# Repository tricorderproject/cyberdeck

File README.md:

# Open Source Science Tricorder Cyberdeck

Explore alien planets with... the open source science tricorder cyberdeck!

# What is this

This is the Github Repository for the **Open Source Science Tricorder Cyberdeck**, an open-source hardware tricorder-like device similar in function to some of the science tricorder devices from the science fiction series Star Trek.  These devices essentially pack a large number of scientific sensors into small hand-held devices, with the (science fiction) intent being that they would be broadly useful for exploring alien worlds, and making new scientific discoveries.

# Table of Contents

- [What is this](#what-is-this)
- [Pictures](#pictures)
- [Frequently Asked Questions](#frequently-asked-questions)
- [Sensor/Hardware List](#sensorhardware-list)
  - [UConsole](#uconsole)
  - [Main Sensors](#main-sensors)
- [Custom PCBs](#custom-pcbs)
  - [PCB: Hamamatsu Microspectrometer Breakout](#pcb-hamamatsu-microspectrometer-breakout)
  - [PCB: ESP32 Breakout](#pcb-esp32-breakout)
  - [PCB: USB Hub Breakout](#pcb-usb-hub-breakout)
- [3D Printed Components](#3d-printed-components)
  - [3D Print: Main Body](#3d-print-main-body)
  - [3D Print: Back Plate](#3d-print-back-plate)
  - [3D Print: Magnetometer Top and Bottom](#3d-print-magnetometer-top-and-bottom)
  - [3D Print: Power Switch](#3d-print-power-switch)
- [Physical Assembly Video](#physical-assembly-video)
- [Firmware (ESP32)](#firmware-esp32)
- [User Interface (Python/UConsole)](#user-interface-pythonuconsole)
- [Design Philosophy and Iterations](#design-philosophy-and-iterations)
  - [Where it was coming from: The Arducorder Mini](#where-it-was-coming-from-the-arducorder-mini)
  - [Iteration 8: Attaching something to an iPhone](#iteration-8-attaching-something-to-an-iphone)
  - [Iteration 9: Teensycorder: Trying to make something that looked like a BlackBerry](#iteration-9-teensycorder-trying-to-make-something-that-looked-like-a-blackberry)
  - [Iteration 10: T-Deck-Corder](#iteration-10-t-deck-corder)
  - [Iteration 11: Initial Cyberdeck explorations with the BTree](#iteration-11-initial-cyberdeck-explorations-with-the-btree)
  - [Iteration 12: A smaller Cyberdeck with the Clockwork Pi PicoCalc](#iteration-12-a-smaller-cyberdeck-with-the-clockwork-pi-picocalc)
  - [Iteration 13: The Open Source Science Tricoder Cyberdeck](#iteration-13-the-open-source-science-tricoder-cyberdeck)
- [Errata](#errata)
  - [Things that are real errors](#things-that-are-real-errors)
  - [Things that I just don't like, or that aren't implemented yet](#things-that-i-just-dont-like-or-that-arent-implemented-yet)
- [AI Usage](#ai-usage)
- [License](#license)
- [Warranty](#warranty)
- [Contact](#contact)

# Pictures

| Main Screen | Spectrometer Screen | Magnetic imager in use (1) | Magnetic imager in use (2) |
| :---: | :---: | :---: | :---: |
|  |  |  |  |
| **Main body with components** | **Main body and back cover** | **Assembled (from back)** | |
|  |  |  | |

# Frequently Asked Questions

**Q1: What is a tricorder?**

A tricorder is a fictional device from the TV series Star Trek, that characters (like Spock) would take with them when they traveled to alien planets.  The tricorder is essentially like a box full of sensors, that would tell them all sorts of things about the environments they would travel to -- like detecting lifeforms, helping them make discoveries, or solve whatever challenges they faced.  There are nominally two kinds of tricorders in the shows -- medical tricorders (that they use for medical diagnosis), and the science tricorders, which they use for scientific/exploratory tasks. 

**Q2. What can it sense?**

This currently has the following sensing capabilities:
- **Thermal Imaging:** a 80x62 Waveshare imager, paired with a regular visible USB camera
- **Visible Spectroscopy:** a Hamamatsu C12666MA microspectrometer, with 256 spectral channels between 340nm and 780nm (in practice, the spectral resolution is about 15nm)
- **Magnetic Field Imager:** An 8x8 (64 pixel) magnetic field camera, provided by the Sparkfun Magnetic Imaging Tile. In practice this can go up to about 20KHz (i.e. 20,000 frames per second). This is also paired with a regular magnetometer (MLX90393) for magnetic field strength and direction.
- **Radiation Spectroscopy:** Where previous open source science tricorders have included radiation sensors, this version includes the Pomelo radiation spectroscopy detector, which uses a scintillation crystal and can differentiate energy levels.
- **Environmental Sensors:** CO2 level, VOC level, Air particulate matter (e.g. PM1/2.5/4/10), ambient temperature, pressure, and humidity.

**Q3: What is a cyberdeck?**

A cyberdeck is the name for essentially small handheld consoles (that include small screens and keyboards), that frequently run full operating systems, and that are often designed to be hackable/modified.  This build is based on the [UConsole by Clockwork Pi](https://www.clockworkpi.com/home-uconsole), which uses a Raspberry Pi compute module -- so it runs linux, and has several cores, about 4GB of RAM, and lots of eMMC storage. 

**Q4: Are there videos showing it functioning?**

Yes, [here is a video on Youtube](https://youtube.com/shorts/MCvRtOt6pII) showing its main functionality. 

**Q5: Is there a video of it being assembled/the inside?**

Yes!  [Here is a video of the inside being put together](https://youtube.com/shorts/LsJ3JqqFUqU), component by component.

**Q6: What does open source mean in the context of open hardware?**

Open hardware is like open source software, except that it is the designs for the device that are openly shared/distributed.  The software/firmware for the device is also included. 

**Q7: Can I build this?**

The honest answer is -- maybe.  This is a prototype, not a product, and there are lots of rough edges.  Historically, most of the utility from the past releases of the open source science tricorders seems to be educational, inspirational (i.e. a real tricorder-like device!), or derivatives (e.g. folks using part of the designs for their own work).  The devices are quite complex to build, and quite expensive.  

**Q8: Why did you build this?**

I grew up watching Star Trek, and my first career choice was always space explorer -- it just turned out that I was born a little early for that to be a common occupation.  But we're not going to get there just sitting around -- we make the future ourselves, so let's build the technology to become future explorers, and make new discoveries together.

**Q9: Who was this made by?**

The Open Source Science Tricorder Project is an open-source educational outreach by Dr. Peter Jansen, a professor at the University of Arizona.  You can learn more about me [here](https://cognitiveai.org/).

**Q10: How many past open source science tricoders have their been?**

I have made about a dozen designs, but only four (including this cyberdeck) have been official 'releases' with significant documentation, the others are generally iterations or prototypes (and some of the failed prototypes for this cyberdeck design are shown in the section below, since it's always exciting to see the development process!). I used to post a design blog on the process, but I am a little busy these days, and don't have a lot of free time, so it now takes me longer to build these things than I am willing to admit. 

The past major releases are the [Mark 1](https://tricorderproject.org/tricorder-mark1.html) and [Mark2 2](https://tricorderproject.org/tricorder-mark2.html) in 2012, the [Arducorder Mini](https://hackaday.io/project/1395-open-source-science-tricorder) in 2014, and then this Cyberdeck in 2026.  In the interim, I also worked on other educational open source hardware projects, like the open source computed tomography (CT) scanners. 

**Q11: How much did this Cyberdeck cost to build?**

The UConsole itself, CM4 compute module, and associated HackerGadgets extension boards, are likely around $300-$400, while the components and build here are likely around $1000.  The visible microspectrometer and the pomelo radiation spectrometer are by far the most expensive components.

# Sensor/Hardware List

The following is the core hardware used in this device, including links to datasheets/etc.

## UConsole

| Component | Description | Link |
| --- | --- | --- |
| UConsole | Clockwork Pi UConsole | [ClockworkPi](https://www.clockworkpi.com/home-uconsole) |
| UConsole Extension | Internal USB Hub, CM5 adapter, battery board | [Hacker Gadgets](https://hackergadgets.com/products/uconsole-upgrade-kit) |

## Main Sensors

| Component | Description | Link |
| --- | --- | --- |
| Thermal Camera | Waveshare Long-wave IR Camera (80x62, USB C) | [Waveshare](https://www.waveshare.com/thermal-camera.htm?sku=25288) |
| USB Camera | Waveshare IMX378 12MP | [Waveshare](https://www.waveshare.com/imx378-12mp-usb-camera-a.htm) |
| Microspectrometer | Hamamatsu C12666MA | [Hamamatsu](https://www.hamamatsu.com/us/en/product/optical-sensors/spectrometers/mini-spectrometer/C12666MA.html) |
| Radiation Sensor | Pomelo Spectroscopic Radiation Detector | [Crowd Supply](https://www.crowdsupply.com/pomelo-instrumentation/pomelo) |
| Air Particle Sensor | Sensirion Particulate Matter Sensor SPS30 | [Sensirion](https://sensirion.com/products/catalog/SPS30) |
| Magnetic Imaging Tile | SparkFun Magnetic Imaging Tile - 8x8 | [SparkFun](https://www.sparkfun.com/sparkfun-magnetic-imaging-tile-8x8.html) |
| Magnetometer | MLX90393 Breakout | [SparkFun](https://www.sparkfun.com/sparkfun-triple-axis-magnetometer-breakout-mlx90393-qwiic.html) |
| CO2 Sensor | SCD40 CO2/Temp/Humidity Breakout | [SparkFun](https://www.sparkfun.com/sparkfun-co2-humidity-and-temperature-sensor-scd40-qwiic.html) |
| Environmental Sensor | BME680 Temp/Pressure/Humidity/VOC | [SparkFun](https://www.sparkfun.com/sparkfun-environmental-sensor-breakout-bme680-qwiic.html) |
| QWIIC Hub | SparkFun Qwiic MultiPort | [SparkFun](https://www.sparkfun.com/sparkfun-qwiic-multiport.html) |

In addition to the hardware above, a handful of custom PCBs are used (described below).

# Custom PCBs

While effort was made to try and have everything in the device be off-the-shelf for this build, a handful of boards were used to make things a little more compact. 

## PCB: Hamamatsu Microspectrometer Breakout

This is a small breakout for the Hamamatsu CD12666MA microspectrometer, that primarily provides a low-profile connector, an op-amp buffer, and handful of filtering passives to help keep the power clean. 

| Board (front) | Board (back) | PCB (top) | PCB (bottom) |
| :---: | :---: | :---: | :---: |
|  |  |  |  |
| **Reflow (toaster oven)** | | | |
|  | | | |

**Design files (EAGLE 9.6.2):** [Schematic (PDF)](hardware/spectrometer/spectrometer-breakout-1c2.pdf) &middot; [Schematic (.sch)](hardware/spectrometer/spectrometer-breakout-1c2.sch) &middot; [Board (.brd)](hardware/spectrometer/spectrometer-breakout-1c2.brd) &middot; [Parts list](hardware/spectrometer/spectrometer-breakout-1b2-partslist.txt)

## PCB: ESP32 Breakout

This is an ESP32 breakout that provides a handy connection between the UConsole (over USB) to most of the other (non-USB) sensors.  The ESP32 board itself is the [Sparkfun ESP32-WROOM USB C](https://www.sparkfun.com/sparkfun-thing-plus-esp32-wroom-usb-c.html). On the left there are small-form connectors for the spectrometer, magnetic imaging tile, and a QWIIC I2C connector.  On the right side are two standard 0.1-spaced headers, one for communicating with the SPS30 air particle sensor, and the other is open, and is intended for a light source for the visible spectrometer. 

| Board | PCB (top) | PCB (bottom) |
| :---: | :---: | :---: |
|  |  |  |

**Design files (EAGLE 9.6.2):** [Schematic (PDF)](hardware/esp32_main_board/clockwork-backpack-1a5.pdf) &middot; [Schematic (.sch)](hardware/esp32_main_board/clockwork-backpack-1a5.sch) &middot; [Board (.brd)](hardware/esp32_main_board/clockwork-backpack-1a5.brd) &middot; [Parts list](hardware/esp32_main_board/clockwork-backpack-1a5-partslist.txt)

## PCB: USB Hub Breakout

This is a breakout for a low-profile USB hub. USB connectors are enormous, and so this further breaks out the [Adafruit CH334F Mini 4-Port USB Hub breakout](https://www.adafruit.com/product/5997) to small JST connectors.  These, unfortunately, are the same JST connectors used by the QWIIC system, which is not a good design decision, so you need to be careful that you're not connecting QWIIC connectors to these 5V usb connections. 

| Board | PCB (top) | PCB (bottom) |
| :---: | :---: | :---: |
|  |  |  |

**Design files (EAGLE 9.6.2):** [Schematic (PDF)](hardware/usb_hub/usb-hub-1b.pdf) &middot; [Schematic (.sch)](hardware/usb_hub/usb-hub-1b.sch) &middot; [Board (.brd)](hardware/usb_hub/usb-hub-1b.brd)

# 3D Printed Components

The enclosure and sensor mounts are 3D printed. The models are authored in OpenSCAD, and both the source and exported STLs are included below.

## 3D Print: Main Body

This is the main physical component, where nearly all of the sensors mount to. It replaces the back of the uConsole, and screws to the uConsole using four M4 screws at the four corners.  Brass inserts, primarily M2.5 (but a few M2 and M3) are used to allow other components to mount to this print.

| Model | With inserts | With components |
| :---: | :---: | :---: |
|  |  |  |

**Design files (OpenSCAD):** [Model (.stl)](openscad/main_body.stl) &middot; [Source (.scad)](openscad/osst_cyberdeck_sept2026.scad)

## 3D Print: Back Plate

The back plate mounts onto the main body, and also allows a handful of environmental sensors to be mounted. These use the Sparkfun breakout mounting pattern (which is nominally about 25x25mm). It also contains the Sparkfun QWIIC hub, which provides additional QWIIC connectors for the ESP32 breakout. 

| Model | With inserts | With components (1) | With components (2) |
| :---: | :---: | :---: | :---: |
|  |  |  |  |

**Design files (OpenSCAD):** [Model (.stl)](openscad/back_cover.stl) &middot; [Source (.scad)](openscad/osst_cyberdeck_sept2026.scad)

## 3D Print: Magnetometer Top and Bottom

This is a (mostly) clamshell design that encloses the magnetic imaging tile, and the magnetometer breakout board.  A handful of brass inserts are used to keep the two sides of the clamshell together. A (very technical) piece of folded paper is used to prevent the magnetometer and magnetic imaging tile boards from short circuiting each other.  The bottom of this piece also includes a hidden duct, that allows the exhaust from the SPS30 air particle sensor to leave the sensor at a right angle, away from the inlet.

| Model (front) | Model (back) | Step 1 | Step 2 |
| :---: | :---: | :---: | :---: |
|  |  |  |  |
| **Step 3** | **Step 4** | **Step 5** | **Step 6** |
|  |  |  |  |
| **Step 7** | **Example Function** | | |
|  |  | | |

**Design files (OpenSCAD):** [Model, front (.stl)](openscad/magtile_front.stl) &middot; [Model, back (.stl)](openscad/magtile_back.stl) &middot; [Source (.scad)](openscad/osst_cyberdeck_sept2026.scad)

## 3D Print: Power Switch

The uConsole has a somewhat hidden power switch, that becomes partically covered by the magnetometer/magnetic imaging tile print above.  This very handy print sits inside the side loop of the magnetic imaging tile print, and when you press it, it presses the real power button. 

| Model | Step 1 | Step 2 |
| :---: | :---: | :---: |
|  |  |  |

**Design files (OpenSCAD):** [Model (.stl)](openscad/powerbutton.stl) &middot; [Source (.scad)](openscad/powerbutton.scad)

# Physical Assembly Video

There's a lot of components in this device, and this short video of stills shows how most of them fit together. 

# Firmware (ESP32)

The ESP32 firmware essentially periodically polls the various sensors (that are not themselves USB sensors), and then sends the measurements from those sensors down a USB-to-Serial connection to the uConsole.  The packets themselves are in `JSONL` format, like below, so they're very easy for whatever software you have on the uConsole to parse them.  For example:

```
{"sensor":"scd4x","payload":{"atmospheric":{"co2_ppm":612,"temp_c":23.4,"humidity_rh_pct":41.2},"timestamp":184532,"error_state":0}}
{"sensor":"mlx90393","payload":{"magnetic":{"x_ut":12.85,"y_ut":-31.42,"z_ut":45.10},"timestamp":184611,"error_state":0}}
{"sensor":"sps30","payload":{"mass":{"PM1_0":2.113,"PM2_5":2.472,"PM4_0":2.601,"PM10":2.665},"number":{"PM0_5":14.201,"PM1_0":16.744,"PM2_5":16.920,"PM4_0":16.951,"PM10":16.963},"timestamp":184702,"error_state":0}}
{"sensor":"magnetic_tile","payload":{"frame":[[2011,2015,...],[2009,2012,...],...],"timestamp":184730,"error_state":0}}
```

Each line is one packet: a `sensor` name, and a `payload` containing that sensor's readings, a `timestamp` (milliseconds since the ESP32 booted), and an `error_state` (0 = OK). The same format is used for the spectrometer (`spec_cd12666ma`, a 256-channel `spectrum` array), the BME688 environmental sensor (`bme688`), and a one-off `firmware` packet sent at boot with the firmware version and build time.

The ESP32 firmware is in: [esp32/uconsole_sensor_backpack_1b/uconsole_sensor_backpack_1b.ino](esp32/uconsole_sensor_backpack_1b/uconsole_sensor_backpack_1b.ino) (an Arduino sketch, with the per-sensor drivers in the same folder).

# User Interface (Python/UConsole)

The user interface on the uConsole polls the various sensors, and displays their readings in a simple user interface.  The user currently selects which screen they'd like to view using the number keys (1-7), and some of the screens have additional functionality, like allowing the user to take baseline measurements (as in for the magnetic imaging tile). 

The interface itself is written in Python, using `pygame` for rendering.

The user interface main entrypoint is here: [src/UserInterfacePygame.py](src/UserInterfacePygame.py) (see [runme.sh](runme.sh), which launches it).

# Design Philosophy and Iterations 

The design philosophy I wanted to explore with this series of iterations of the *open source science tricorder* project was to make the designs easier for others to replicate, nominally by minimizing reliance on custom printed circuit boards and other complex manufacturing processes.  Because most of the complexity comes from displays, input, and so forth, I ended up exploring this in the context of using other devices to supply the input/output, while trying to "bolt" sensors onto them.  In the end, I'm not entirely sure I met the goal -- and the device is much larger than it needs to be, because of all the space required to have all the sensors be off-the-shelf -- but ultimately, I'm pretty happy with it. 

What you mostly see is the end design, but this took **many** iterations over quite a few years to get to where it is.  Here is a sneak peak at some of those design iterations. 

## Where it was coming from: The Arducorder Mini

The Arducorder mini is a beautifully designed but entirely custom device, described here: [Arducorder Mini build logs](https://hackaday.io/project/1395-open-source-science-tricorder)

| Arducorder Mini (1) | Arducorder Mini (2) | Arducorder Mini (3) | Arducorder Mini (4) |
| :---: | :---: | :---: | :---: |
|  |  |  |  |

## Iteration 8: Attaching something to an iPhone

My first exploration was building something that would attach to the back of (my) iPhone, using a Raspberry Pi Zero W (running a webserver) to communicate with the iPhone over Wifi, and an Arduino Mini to communicate with all the sensors.  This one ended up about 90% built, but it just seemed like a giant kludge, and I discarded it before making an enclosure.

While the whole device didn't end up working out, one of the outcomes of this iteration was the development of a successful magnetic imaging tile, which ended up being used in future iterations.

The build logs of Iteration 8 are available [here on hackaday.io](https://hackaday.io/project/18518-iteration-8/log/164805-a-new-motherboard-design-now-with-more-pi), with the broader project available [here](https://hackaday.io/project/18518-iteration-8).

| Iteration 8 Prototype | Atmospheric Sensor Prototype | Magnetic Imaging Tile Prototype |
| :---: | :---: | :---: |
|  |  |  |

## Iteration 9: Teensycorder: Trying to make something that looked like a BlackBerry

Then, I abandoned some of my design principles (as one sometimes does) and decided to try and make something that just used a display and keyboard that was already broken out.  

A post on the Teensycorder is available here: [build log on hackaday.io](https://hackaday.io/project/18518-iteration-8/log/213613-back-at-it-with-the-teensycorder)

| Teensycorder (1) | Teensycorder (2) | Teensycorder (3) | Teensycorder (4) |
| :---: | :---: | :---: | :---: |
|  |  |  |  |
| **Teensycorder (5)** |  |  |  |
|  |  |  |  |

## Iteration 10: T-Deck-Corder

I liked the *idea* of the teensycorder, but I didn't really like how big it was turning out.  Around the same time, the [T-Deck (a small blackberry-like device)](https://lilygo.cc/en-us/products/t-deck-plus-1) was released, and I tinkered with making a backpack for it.  But in the end, the challenges of trying to fit so many sensors into such a small space didn't quite work out -- but I did like the form factor a great deal. 

I ended up not taking too many pictures of this one or its board.

## Iteration 11: Initial Cyberdeck explorations with the Raspberry Pi CMx Tablets

Around this time, Cyberdeck builds started to pop up -- folks were bolting found-keyboards onto found Raspberry Pi compute module-based tablets.  I had a go at building one of these, and these initial iterations are what convinced me that there might be something to the Cyberdeck format.  But there were many problems: It's such a kludge of parts, the keyboards (which are bluetooth!) often have pairing and even powering challenges when you disassemble them, and the whole thing was just *big*.  Most of the room of the huge device was spent trying to get all these large parts to fit together for the console, rather than getting sensors and such in there. 

| Tablet Prototype (1) | Tablet Prototype (2) | Many prototype prints around this time |
| :---: | :---: | :---: |
|  |  |  |

## Iteration 12: A smaller Cyberdeck with the Clockwork Pi PicoCalc

Clockwork Pi released a small cyberdeck called the [PicoCalc](https://www.clockworkpi.com/picocalc), and I was actually fairly convinced that this would be the way forward.  The form factor was smaller than the "found tablet + keyboard", it had a keyboard and a display, and it was very hackable.  But it was based on a small and underpowered microcontroller, which would have significant issues for interfacing with a thermal camera, regular camera, and lots of other peripherals.  So I made a backpack that would replace the microcontroller with a Raspberry Pi Zero W, and use an Arduino as the primary sensor interface.  A 3D printed enclosure ended up being the mount for many of the sensors. 

I actually didn't hate this one, and thought it would be the release.  But the screen resolution (which I think was 320x320, or some other small resolution) ended up just being /too small/ to work with -- you really couldn't easily run X Windows, and I wanted to be able to just use standard software/UI libraries rather than writing everything from scratch again.  So I ended up abandoning this one while it was nearly 90-95% finished.

One (very interesting) aspect of this prototype was focusing on trying to have the visible spectrometer be in transmission mode by default. The big aperture in the side of the device is meant for you to slide a sample container for the spectrometer in it, with a light source on one side, and the spectrometer on the other.  If you wanted to use the spectrometer openly instead of in transmission mode, there'd be a small faux sample container that'd have a mirror in it that would point to the outside world.

There are a few early posts on this one [here on the clockwork pi forum](https://forum.clockworkpi.com/t/raspberry-pi-zero-2-on-picocalc/17946/35). 

| PicoCalc (1) | PicoCalc (2) | PicoCalc (3) | PicoCalc (4) |
| :---: | :---: | :---: | :---: |
|  |  |  |  |
| **PicoCalc (5)** | **PicoCalc (6)** |  |  |
|  |  |  |  |

## Iteration 13: The Open Source Science Tricoder Cyberdeck

Ultimately the one this repository is about ended up being the one that really worked.  Moving from the `Picocalc` to the `UConsole` provided much more display resolution, and the Raspberry Pi CM4 compute module provided much more compute power than the Raspberry Pi Zero W.  The sensors could be physically added to the back as a sort of custom backpack, rather being all over the place on the Picocalc version, which ended up working very well.

Here are a few early pictures, where I tried to attach a stock cooler -- which ended up needing a truly huge amount of space in the design (so I abandoned it for a time, thinking I wouldn't need a cooler).  It turns out it does run a little warm without a cooler, and would need some kind of cooling in a future iteration.

| Early build (1) | Early build (2) |
| :---: | :---: |
|  |  |

# Errata

## Things that are real errors

1. **Cooling:** The Raspberry Pi compute modules put out real heat, and while you can run them without a cooler for a while, they do get hot -- and will eventually thermally throttle.  This needs some kind of cooling solution, nominally a copper cooler that extends out with a small fan or something similar.

2. **Silkscreen Misprint:** In an earlier version of the ESP32 board (which is shown in the pictures), the white silkscreen text on the PCB swaps which connector should be for the spectrometer, and which connector should be for the magnetic imaging tile.  The connector closest to the middle of the board should be the spectrometer, and the connector closest to the corner of the board should be the magnetic imaging tile. This should be corrected on the latest board file.  

## Things that I just don't like, or that aren't implemented yet

1. **Battery:** The battery does not run for long.  You get maybe an hour or two.  Having smart power features for the sensors would be ideal.
2. **Magnetic Imaging Tile Framerate:** I designed the magnetic imaging tile to have very fast framerates (e.g. up to 20KHz), but the current refresh rate in the interface is only around 1 frame per second.  This is because it's connected to the ESP32, which is constantly polling all sensors in a round-robbin.  The ESP32 firmware needs a separate mode that allows just focusing on the imaging tile for a short while, so that it can record high-speed captures.  It's a minimal amount of work, it's just not implemented yet.
3. **Transmission spectroscopy for visible spectrometer:** I have spent more time than I'm willing to admit thinking about how to put on a proper light source that can be easily mounted/unmounted for transmission spectroscopy.  There is an unused header on the ESP32 breakout for this purpose, but I haven't found a good solution that I like yet.
4. **Wifi Antenna:** I haven't found a great place for the uConsole Wifi antenna yet, which is currently tucked (but not stuck) near the magnetic tile. 
5. **USB Connectors:** It is a genuinely poor design decision for me to use the same QWIIC connectors for the USB hub connectors, because it allows for folks to easily make costly mistakes (e.g. plugging a 3.3V QWIIC connection into a 5V USB connection, and potentially blowing up the QWIIC part).  But the QWIIC connectors and cables were readily available and easy-to-use, and I did it.  My deepest apologies.

# AI Usage

My recollection is that the ESP32 firmware is primarily human written (by me, using libraries authored by myself and others), while the Python user interface is mostly AI generated.  AI models were also used in debugging in the final stages (thank you, Claude, for noticing that I had swapped two pins on the magnetic imaging tile driver, ending my debugging session in an hour instead of many hours). 

# License

The parts of this that are non-code/physical designs (e.g. the 3D prints, the PCBs, the documentation) are licensed [Creative Commons BY 4.0](https://creativecommons.org/licenses/by/4.0/).

The ESP32 firmware essentially stitches together existing libraries with an interface; there is not enough substantial code there to warrant it needing a separate license.  Similarly, the Python user interface is mostly AI generated, and while this is a new legal area, my best understanding is that such code is likely not subject to copyright. 

All of the above is not meant to in any way limit the disclaimer of warranty for all aspects of this project, which is described below.

# Warranty

TLDR: This is a prototype, not a product, and the information in this repository/project may have genuine risks to use.  The author provides no warranty of any kind, and you assume all risks and responsibilities. 

The following is Section 5 of the [Creative Commons Attribution 4.0 International legal code](https://creativecommons.org/licenses/by/4.0/legalcode), reproduced verbatim, and adopted here as the warranty disclaimer for every part of this project (hardware, firmware, software, documentation, etc.):

```
Section 5 -- Disclaimer of Warranties and Limitation of Liability.

  a. UNLESS OTHERWISE SEPARATELY UNDERTAKEN BY THE LICENSOR, TO THE
     EXTENT POSSIBLE, THE LICENSOR OFFERS THE LICENSED MATERIAL AS-IS
     AND AS-AVAILABLE, AND MAKES NO REPRESENTATIONS OR WARRANTIES OF
     ANY KIND CONCERNING THE LICENSED MATERIAL, WHETHER EXPRESS,
     IMPLIED, STATUTORY, OR OTHER. THIS INCLUDES, WITHOUT LIMITATION,
     WARRANTIES OF TITLE, MERCHANTABILITY, FITNESS FOR A PARTICULAR
     PURPOSE, NON-INFRINGEMENT, ABSENCE OF LATENT OR OTHER DEFECTS,
     ACCURACY, OR THE PRESENCE OR ABSENCE OF ERRORS, WHETHER OR NOT
     KNOWN OR DISCOVERABLE. WHERE DISCLAIMERS OF WARRANTIES ARE NOT
     ALLOWED IN FULL OR IN PART, THIS DISCLAIMER MAY NOT APPLY TO YOU.

  b. TO THE EXTENT POSSIBLE, IN NO EVENT WILL THE LICENSOR BE LIABLE
     TO YOU ON ANY LEGAL THEORY (INCLUDING, WITHOUT LIMITATION,
     NEGLIGENCE) OR OTHERWISE FOR ANY DIRECT, SPECIAL, INDIRECT,
     INCIDENTAL, CONSEQUENTIAL, PUNITIVE, EXEMPLARY, OR OTHER LOSSES,
     COSTS, EXPENSES, OR DAMAGES ARISING OUT OF THIS PUBLIC LICENSE OR
     USE OF THE LICENSED MATERIAL, EVEN IF THE LICENSOR HAS BEEN
     ADVISED OF THE POSSIBILITY OF SUCH LOSSES, COSTS, EXPENSES, OR
     DAMAGES. WHERE A LIMITATION OF LIABILITY IS NOT ALLOWED IN FULL OR
     IN PART, THIS LIMITATION MAY NOT APPLY TO YOU.

  c. The disclaimer of warranties and limitation of liability provided
     above shall be interpreted in a manner that, to the extent
     possible, most closely approximates an absolute disclaimer and
     waiver of all liability.
```

# Contact

For questions, please use either Github Issues or `peter@tricorderproject.org` .

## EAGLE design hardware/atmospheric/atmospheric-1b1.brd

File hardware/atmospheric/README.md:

Note: This atmospheric breakout board is untested.

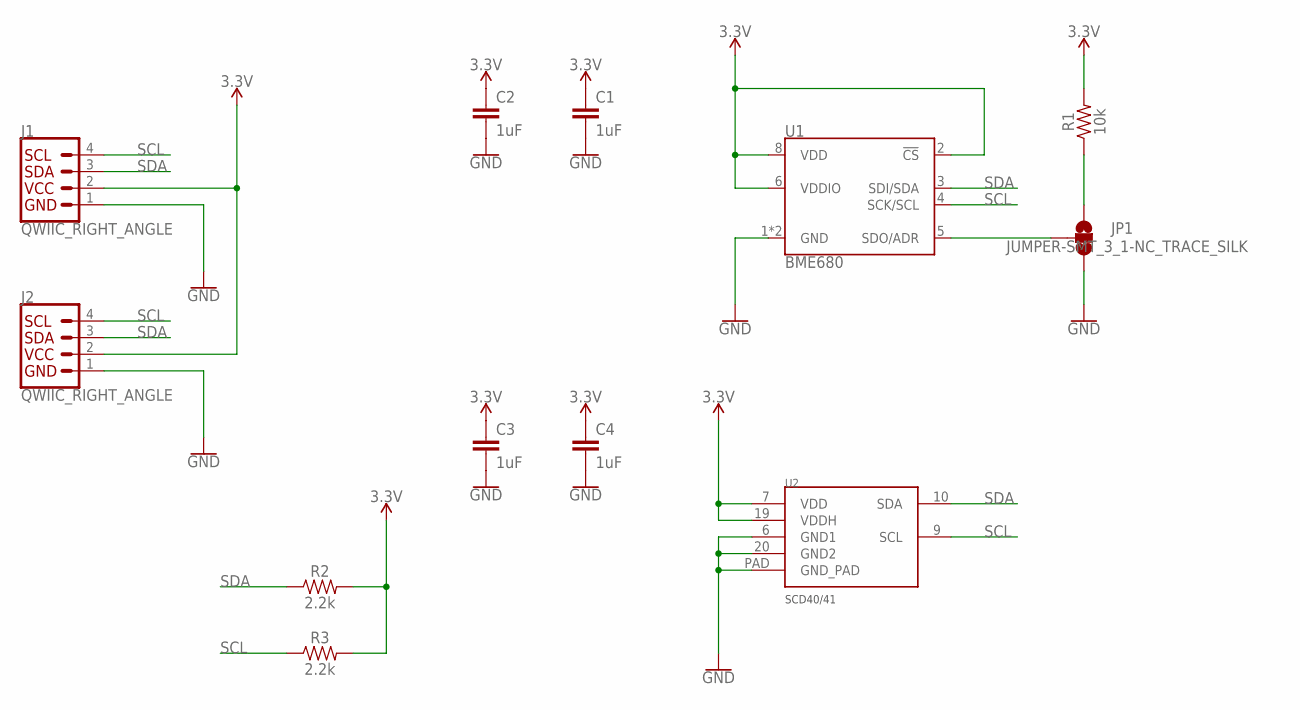
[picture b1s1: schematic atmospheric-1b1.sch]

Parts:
C1, C2, C3, C4: 1uF; 0603
J1, J2: QWIIC_RIGHT_ANGLE; JST04_1MM_RA
JP1: JUMPER-SMT_3_1-NC_TRACE_SILK; SMT-JUMPER_3_1-NC_TRACE_SILK
R1: 10k; 0603
R2, R3: 2.2k; 0603
U1: BME680; LGA3.0X3.0
U2: SCD4X

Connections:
3.3V: C1.1, C2.1, C3.1, C4.1, J1.2, J2.2, R1.2, R2.2, R3.2, U1.2 (!CS), U1.6 (VDDIO), U1.8 (VDD), U2.7 (VDD), U2.19 (VDDH)
GND: C1.2, C2.2, C3.2, C4.2, J1.1, J2.1, JP1.3, U1.1 (GND), U1.7 (GND), U2.6 (GND1), U2.20 (GND2), U2.PAD (GND_PAD)
unnamed: JP1.2, U1.5 (SDO/ADR)
unnamed: JP1.1, R1.1
SCL: J1.4, J2.4, R3.1, U1.4 (SCK/SCL), U2.9 (SCL)
SDA: J1.3, J2.3, R2.1, U1.3 (SDI/SDA), U2.10 (SDA)

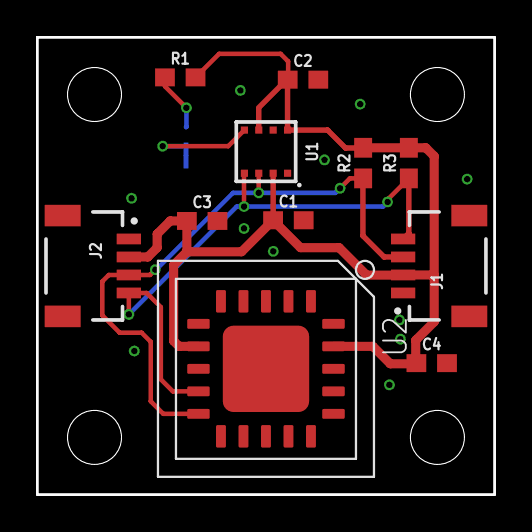
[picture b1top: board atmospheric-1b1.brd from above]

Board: 2 copper layers, 25.4 x 25.4 mm, 12 parts (1 on the bottom side), 6 nets.

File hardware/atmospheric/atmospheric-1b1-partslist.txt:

Partlist

Exported	from	atmospheric-1b1.sch	at	6/21/25	4:54	PM

EAGLE	Version	9.6.2	Copyright	(c)	1988-2020	Autodesk,	Inc.

Assembly	variant:	

Part	Value	Device	Package	Library	Sheet

C1	1uF	CAP-0603	0603	SparkFun-Capacitors	1
C2	1uF	CAP-0603	0603	SparkFun-Capacitors	1
C3	1uF	CAP-0603	0603	SparkFun-Capacitors	1
C4	1uF	CAP-0603	0603	SparkFun-Capacitors	1
J1	QWIIC_RIGHT_ANGLE	QWIIC_CONNECTORJS-1MM	JST04_1MM_RA	SparkFun-Connectors	1
J2	QWIIC_RIGHT_ANGLE	QWIIC_CONNECTORJS-1MM	JST04_1MM_RA	SparkFun-Connectors	1
JP1	JUMPER-SMT_3_1-NC_TRACE_SILK	JUMPER-SMT_3_1-NC_TRACE_SILK	SMT-JUMPER_3_1-NC_TRACE_SILK	SparkFun-Jumpers	1
R1	10k	RESISTOR0603	0603	SparkFun-Resistors	1
R2	10k	RESISTOR0603	0603	SparkFun-Resistors	1
R3	10k	RESISTOR0603	0603	SparkFun-Resistors	1
U1	BME680	BME680-LGA	LGA3.0X3.0	SparkFun-Sensors	1
U2	SCD4X	SCD4X	SCD4X	notes1a	1

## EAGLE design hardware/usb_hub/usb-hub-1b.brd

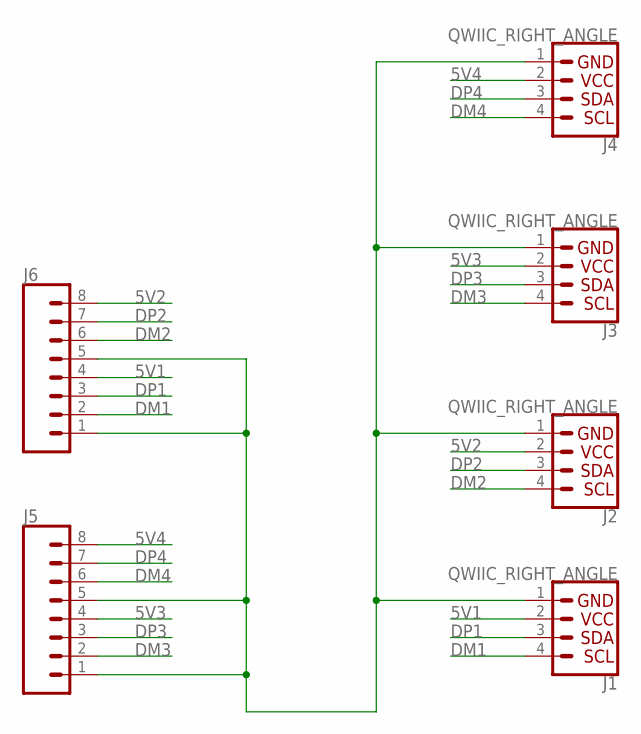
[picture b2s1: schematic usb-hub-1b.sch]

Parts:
J1, J2, J3, J4: QWIIC_RIGHT_ANGLE; JST04_1MM_RA
J5, J6: CONN_08LOCK; 1X08_LOCK

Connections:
5V1: J1.2, J6.4
5V2: J2.2, J6.8
5V3: J3.2, J5.4
5V4: J4.2, J5.8
DM1: J1.4, J6.2
DM2: J2.4, J6.6
DM3: J3.4, J5.2
DM4: J4.4, J5.6
DP1: J1.3, J6.3
DP2: J2.3, J6.7
DP3: J3.3, J5.3
DP4: J4.3, J5.7
GND: J1.1, J2.1, J3.1, J4.1, J5.1, J5.5, J6.1, J6.5

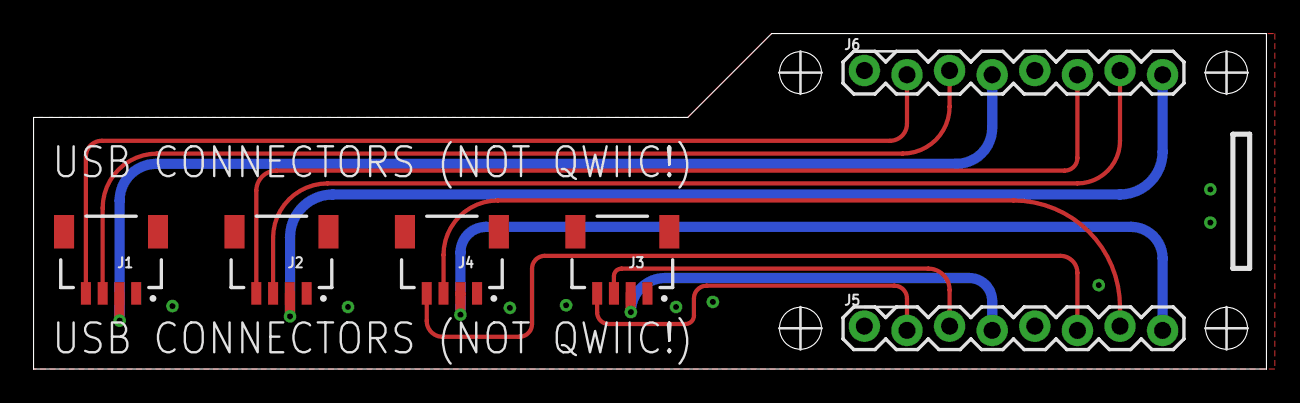
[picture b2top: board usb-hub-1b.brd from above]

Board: 2 copper layers, 73.5 x 20.0 mm, 6 parts (0 on the bottom side), 13 nets.

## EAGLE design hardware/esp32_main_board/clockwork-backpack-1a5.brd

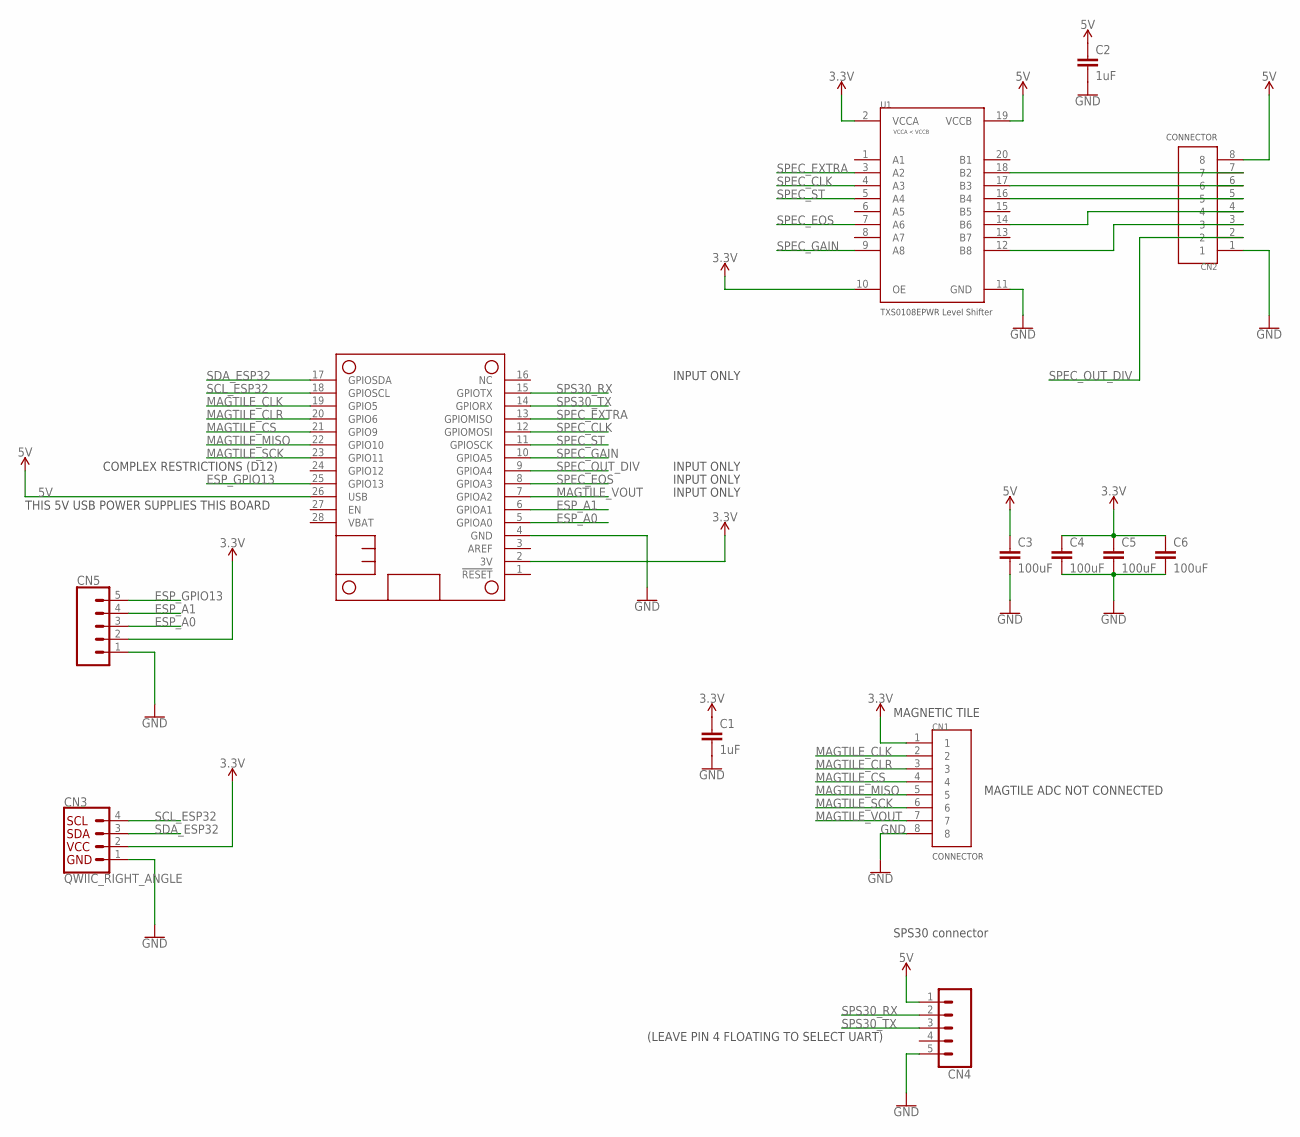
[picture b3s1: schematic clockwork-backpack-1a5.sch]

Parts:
C1, C2: 1uF; 0603
C3, C4, C5, C6: 100uF; 1206
CN1, CN2: CON-SM08B-SRSS-TB
CN3: QWIIC_RIGHT_ANGLE; JST04_1MM_RA
CN4, CN5: CONN_05LOCK; 1X05_LOCK
U1: TXS0108EPWR; TSSOP-20
U2: FEATHERWING_NODIM; FEATHERWING_DIM

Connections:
3.3V: C1.1, C4.1, C5.1, C6.1, CN1.1, CN3.2, CN5.2, U1.2 (VCCA), U1.10 (OE), U2.2 (3V)
5V: C2.1, C3.1, CN2.8, CN4.1, U1.19 (VCCB), U2.26 (USB)
ESP_A0: CN5.3, U2.5 (GPIOA0)
ESP_A1: CN5.4, U2.6 (GPIOA1)
ESP_GPIO13: CN5.5, U2.25 (GPIO13)
GND: C1.2, C2.2, C3.2, C4.2, C5.2, C6.2, CN1.8, CN2.1, CN3.1, CN4.5, CN5.1, U1.11 (GND), U2.4 (GND)
MAGTILE_CLK: CN1.2, U2.19 (GPIO5)
MAGTILE_CLR: CN1.3, U2.20 (GPIO6)
MAGTILE_CS: CN1.4, U2.21 (GPIO9)
MAGTILE_MISO: CN1.5, U2.22 (GPIO10)
MAGTILE_SCK: CN1.6, U2.23 (GPIO11)
MAGTILE_VOUT: CN1.7, U2.7 (GPIOA2)
unnamed: CN2.7, U1.18 (B2)
unnamed: CN2.3, U1.12 (B8)
unnamed: CN2.4, U1.14 (B6)
unnamed: CN2.6, U1.17 (B3)
unnamed: CN2.5, U1.16 (B4)
SCL_ESP32: CN3.4, U2.18 (GPIOSCL)
SDA_ESP32: CN3.3, U2.17 (GPIOSDA)
SPEC_CLK: U1.4 (A3), U2.12 (GPIOMOSI)
SPEC_EOS: U1.7 (A6), U2.8 (GPIOA3)
SPEC_EXTRA: U1.3 (A2), U2.13 (GPIOMISO)
SPEC_GAIN: U1.9 (A8), U2.10 (GPIOA5)
SPEC_OUT_DIV: CN2.2, U2.9 (GPIOA4)
SPEC_ST: U1.5 (A4), U2.11 (GPIOSCK)
SPS30_RX: CN4.2, U2.15 (GPIOTX)
SPS30_TX: CN4.3, U2.14 (GPIORX)

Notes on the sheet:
SPS30 connector
MAGNETIC TILE
MAGTILE ADC NOT CONNECTED
INPUT ONLY
COMPLEX RESTRICTIONS (D12)
(LEAVE PIN 4 FLOATING TO SELECT UART)
THIS 5V USB POWER SUPPLIES THIS BOARD

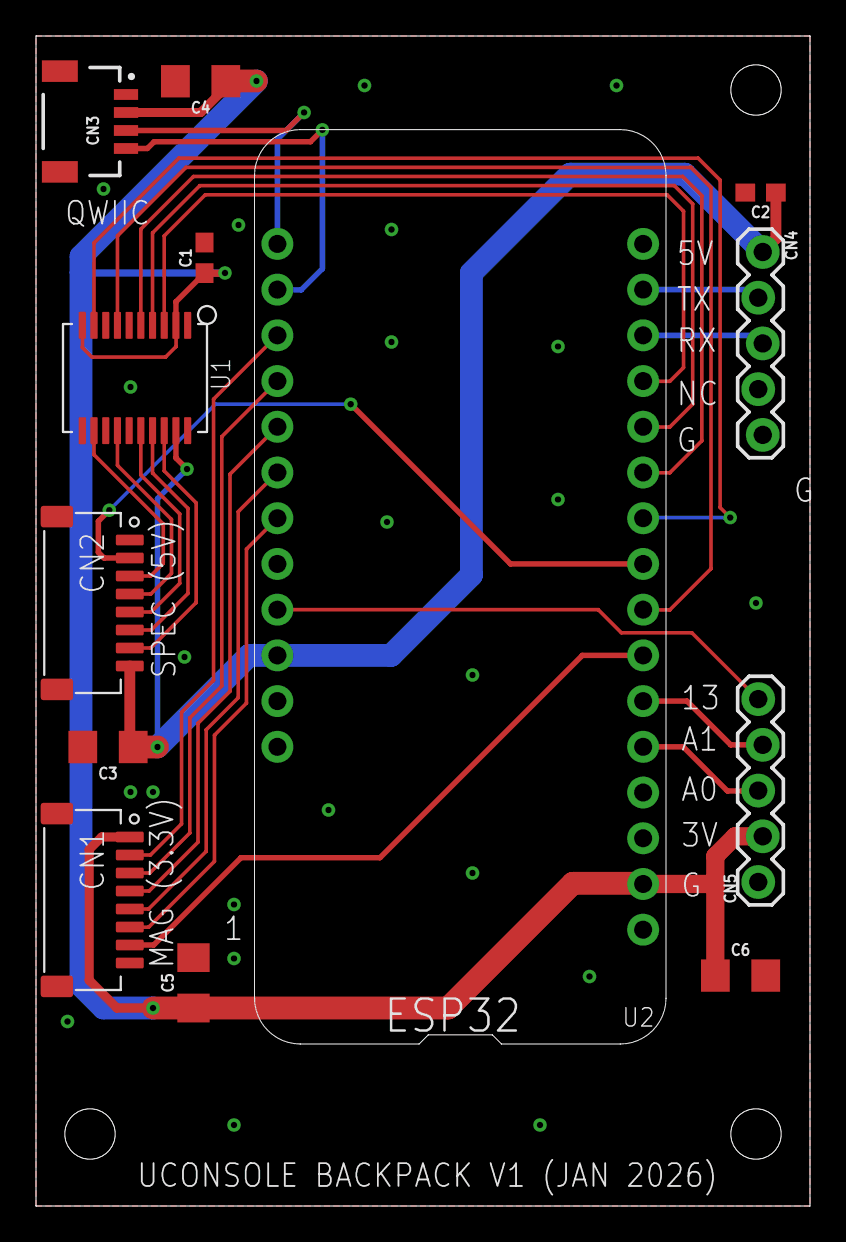
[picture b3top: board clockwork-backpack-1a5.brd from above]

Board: 2 copper layers, 43.0 x 65.0 mm, 13 parts (0 on the bottom side), 27 nets.

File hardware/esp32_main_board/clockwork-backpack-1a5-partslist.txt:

Partlist

Exported from clockwork-backpack-1a4.sch at 1/8/26 11:38 AM

EAGLE Version 9.6.2 Copyright (c) 1988-2020 Autodesk, Inc.

Assembly variant: 

Part     Value             Device                Package           Library             Sheet

C1       1uF               CAP-0603              0603              SparkFun-Capacitors 1
C2       1uF               CAP-0603              0603              SparkFun-Capacitors 1
C3       100uF             CAP-1206              1206              SparkFun-Capacitors 1
C4       100uF             CAP-1206              1206              SparkFun-Capacitors 1
C5       100uF             CAP-1206              1206              SparkFun-Capacitors 1
C6       100uF             CAP-1206              1206              SparkFun-Capacitors 1
CN1      CON-SM08B-SRSS-TB CON-SM08B-SRSS-TB     CON-SM08B-SRSS-TB notes1a             1
CN2      CON-SM08B-SRSS-TB CON-SM08B-SRSS-TB     CON-SM08B-SRSS-TB notes1a             1
CN3      QWIIC_RIGHT_ANGLE QWIIC_CONNECTORJS-1MM JST04_1MM_RA      SparkFun-Connectors 1
CN4                        CONN_05LOCK           1X05_LOCK         SparkFun-Connectors 1
CN5                        CONN_05LOCK           1X05_LOCK         SparkFun-Connectors 1
U1       TXS0108EPWR       TXS0108EPWR           TSSOP-20          notes1a             1
U2       FEATHERWING_NODIM FEATHERWING_NODIM     FEATHERWING_DIM   notes1a             1

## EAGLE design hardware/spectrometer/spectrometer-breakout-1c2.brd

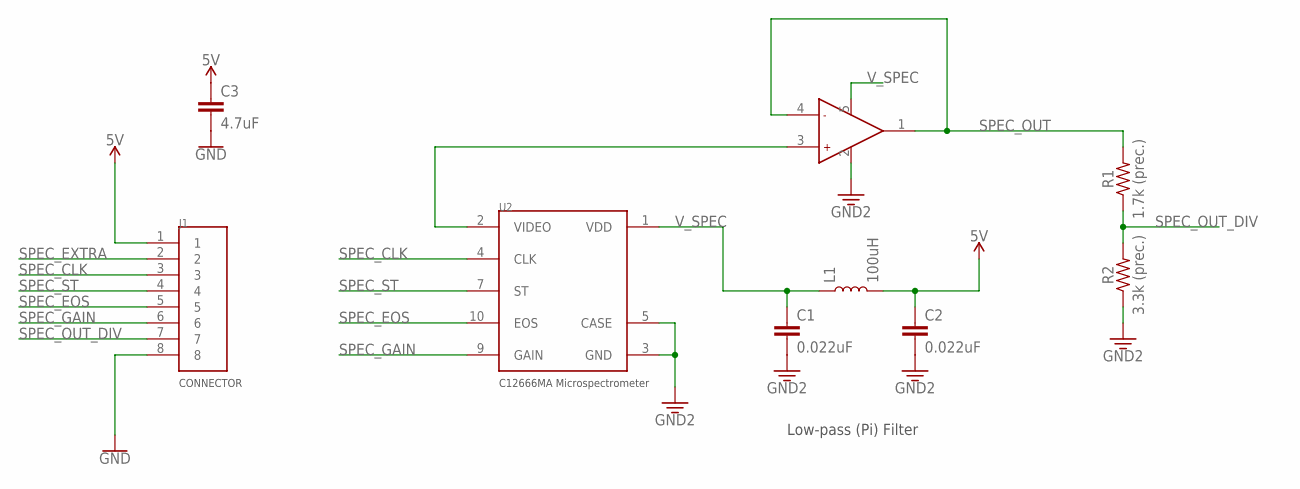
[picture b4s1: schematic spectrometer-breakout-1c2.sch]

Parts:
C1, C2: 0.022uF; 0603
C3: 4.7uF; 0603
J1: CON-SM08B-SRSS-TB
L1: 100uH; 0603
R1: 1.7k (prec.); 0603
R2: 3.3k (prec.); 0603
U1: OPA344NA/250; SOT3-5
U2: C12666MA

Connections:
5V: C2.1, C3.1, J1.1, L1.2
GND: C1.2, C2.2, C3.2, J1.8, R2.1, U1.2 (GND), U2.3 (GND), U2.5 (CASE)
unnamed: U1.3 (+), U2.2 (VIDEO)
SPEC_CLK: J1.3, U2.4 (CLK)
SPEC_EOS: J1.5, U2.10 (EOS)
SPEC_EXTRA: J1.2
SPEC_GAIN: J1.6, U2.9 (GAIN)
SPEC_OUT: R1.2, U1.1 (OUT), U1.4 (-)
SPEC_OUT_DIV: J1.7, R1.1, R2.2
SPEC_ST: J1.4, U2.7 (ST)
V_SPEC: C1.1, L1.1, U1.5 (VCC), U2.1 (VDD)

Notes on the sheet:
Low-pass (Pi) Filter

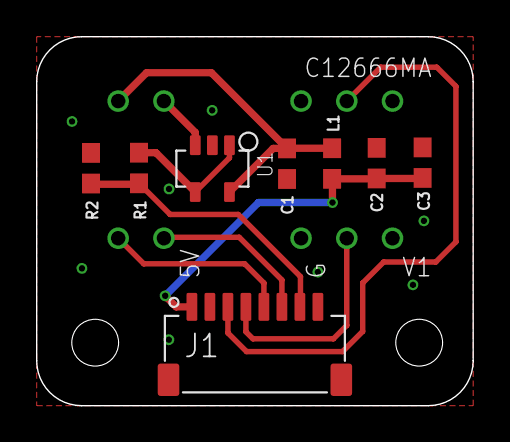
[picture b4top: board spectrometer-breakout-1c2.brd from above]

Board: 2 copper layers, 24.2 x 20.5 mm, 9 parts (1 on the bottom side), 10 nets.

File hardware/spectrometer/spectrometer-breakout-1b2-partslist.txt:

Partlist

Exported	from	spectrometer-breakout-1c2.sch	at	6/21/25	4:54	PM

EAGLE	Version	9.6.2	Copyright	(c)	1988-2020	Autodesk,	Inc.

Assembly	variant:	

Part	Value	Device	Package	Library	Sheet

C1	0.022uF	CAP-0603	0603	SparkFun-Capacitors	1
C2	0.022uF	CAP-0603	0603	SparkFun-Capacitors	1
C3	4.7uF	CAP-0603	0603	SparkFun-Capacitors	1
J1	CON-SM08B-SRSS-TB	CON-SM08B-SRSS-TB	CON-SM08B-SRSS-TB	notes1a	1
L1	100uH	INDUCTORDNP	0603	SparkFun-Coils	1
R1	1.7k	(prec.)	RESISTOR0603	0603	SparkFun-Resistors	1
R2	3.3k	(prec.)	RESISTOR0603	0603	SparkFun-Resistors	1
U1	OPA344NA/250	OPA344NA/250	SOT3-5	notes1a	1
U2	C12666MA	C12666MA	C12666MA	notes1a	1

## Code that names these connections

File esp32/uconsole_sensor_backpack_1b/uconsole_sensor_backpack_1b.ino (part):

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const byte PIN_ANALOG = A2;

// Pin mapping for the clockwork-backpack-1a4 main board with a SparkFun ESP32 Thing Plus C in the
// Feather socket.  The schematic labels the socket by Feather position (GPIO5, GPIO6, GPIO9, ...);
// the ESP32 GPIO that the Thing Plus C actually has at each of those positions is used here.
//   Feather pos.  Thing Plus C GPIO   Tile signal
//   GPIO5         14                  CLK  (counter clock)
//   GPIO6         32                  CLR  (counter clear)
//   GPIO9         15                  CS   (AD7680, unused)
//   GPIO10        33                  MISO (AD7680, unused)
//   GPIO11        27                  SCK  (AD7680, unused)
//   A2            34                  OUT  (analog)
#define PIN_CLR   32
#define PIN_CLK   14
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
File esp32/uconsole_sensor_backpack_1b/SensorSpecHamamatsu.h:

// SensorSpecHamamatsu.h
#if !defined(SENSOR_SPEC_C12666_h) 
#define SENSOR_SPEC_C12666_h

//#include <wprogram.h>
#include <Arduino.h>

// Number of spectral channels
#define SPEC_CHANNELS    256

// Pin mappings
#define SPEC_GAIN        35
#define SPEC_EOS         39
#define SPEC_ST          18
#define SPEC_CLK         23
#define SPEC_ANALOG_IN   A4


class SensorSpecHamamatsu {
  // Variables  
  public:
  uint16_t data[SPEC_CHANNELS];
  uint16_t intTime;      // Integration (sampling) time    
  uint8_t gain;          // High/low gain
  unsigned long timeSampled;    // The time the last measurement was taken (measured with millis())

  // Constructor/Destructor
  SensorSpecHamamatsu();
  ~SensorSpecHamamatsu();
  
  // Setup methods
  boolean begin();
  void setIntTime(uint16_t time);  
  void setGain(uint8_t highLow);  
    
  // Low-level communication 
  uint16_t readAD7940();
  void readSpectrometer();
  
  void exportJSON(Stream &port);

  // Debug 
  void debugPrint();
};

#endif

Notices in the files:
parts and their libraries:
SparkFun-Capacitors: Licensing: Creative Commons ShareAlike 4.0 International - https://creativecommons.org/licenses/by-sa/4.0
